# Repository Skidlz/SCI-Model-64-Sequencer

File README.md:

# SCI-Model-64-Sequencer
Sequential Circuits Model 64 Sequencer for Commodore 64

## Parts
At the time or writing, most of the parts are still available at Jameco.

They offer the H11L1 can be used in place of the PC900, and 68B21 instead of the 68A21.

## Schematic

## PCB

## Case

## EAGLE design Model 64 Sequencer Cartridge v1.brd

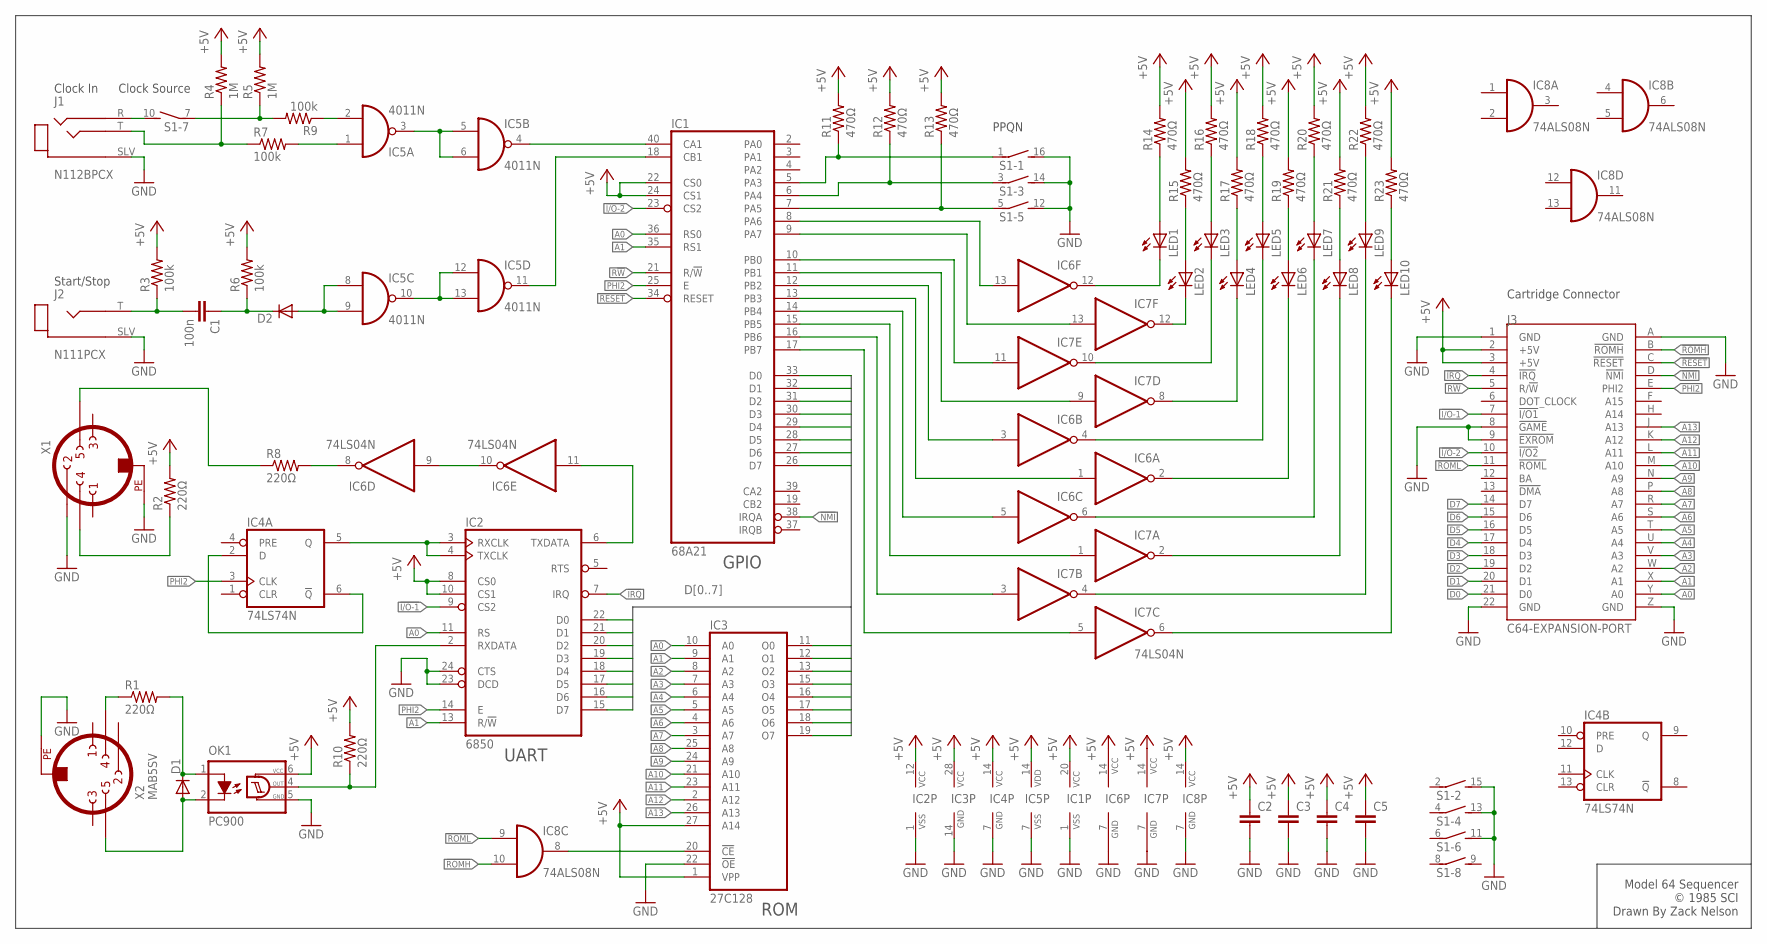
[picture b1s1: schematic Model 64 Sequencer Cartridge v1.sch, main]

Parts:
C1: 100n; C050-024X044
C2, C3, C4, C5: C-EU050-024X044; C050-024X044
D1, D2: DIODE-D-7.5; D-7.5
IC1: 68A21; DIL40
IC2: 6850; DIL24
IC3: 27C128; DIL28
IC4: 74LS74N; DIL14
IC5: 4011N; DIL14
IC6, IC7: 74LS04N; DIL14
IC8: 74ALS08N; DIL14
J1: N112BPCX; SWITCHCRAFT_N112BPCX
J2: N111PCX; SWITCHCRAFT_N111PCX
J3: C64-EXPANSION-PORT; EXPANSIO_SQ
LED1, LED2, LED3, LED4, LED5, LED6, LED7, LED8, LED9, LED10: LED3MM
OK1: PC900; DIL06
R1, R2, R8, R10: 220Ω; 0207/12
R3, R6, R7, R9: 100k; 0207/12
R4, R5: 1M; 0207/12
R11, R12, R13, R14, R15, R16, R17, R18, R19, R20, R21, R22, R23: 470Ω; 0207/12
S1: DIP08S
X1, X2: MAB5SV

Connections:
!I/O-1: IC2.9 (CS2), J3.7 (!I/O1)
!I/O-2: IC1.23 (CS2), J3.10 (!I/O2)
!IRQ: IC2.7 (IRQ), J3.4 (!IRQ)
!NMI: IC1.38 (IRQA), J3.D (!NMI)
!RESET: IC1.34 (RESET), J3.C (!RESET)
!ROMH: IC8.10 (I1), J3.B (!ROMH)
!ROML: IC8.9 (I0), J3.11 (!ROML)
+5V: C2.1, C3.1, C4.1, C5.1, IC1.20 (VCC), IC1.22 (CS0), IC1.24 (CS1), IC2.8 (CS0), IC2.10 (CS1), IC2.12 (VCC), IC3.1 (VPP), IC3.27 (A14), IC3.28 (VCC), IC4.14 (VCC), IC5.14 (VDD), IC6.14 (VCC), IC7.14 (VCC), IC8.14 (VCC), J3.2 (+5V), J3.3 (+5V), OK1.6 (VCC), R2.2, R3.2, R4.2, R5.2, R6.2, R10.2, R11.2, R12.2, R13.2, R14.2, R15.2, R16.2, R17.2, R18.2, R19.2, R20.2, R21.2, R22.2, R23.2
A0: IC1.36 (RS0), IC2.11 (RS), IC3.10 (A0), J3.Y (A0)
A1: IC1.35 (RS1), IC2.13 (R/!W), IC3.9 (A1), J3.X (A1)
A2: IC3.8 (A2), J3.W (A2)
A3: IC3.7 (A3), J3.V (A3)
A4: IC3.6 (A4), J3.U (A4)
A5: IC3.5 (A5), J3.T (A5)
A6: IC3.4 (A6), J3.S (A6)
A7: IC3.3 (A7), J3.R (A7)
A8: IC3.25 (A8), J3.P (A8)
A9: IC3.24 (A9), J3.N (A9)
A10: IC3.21 (A10), J3.M (A10)
A11: IC3.23 (A11), J3.L (A11)
A12: IC3.2 (A12), J3.K (A12)
A13: IC3.26 (A13), J3.J (A13)
D0: IC1.33 (D0), IC2.22 (D0), IC3.11 (O0), J3.21 (D0)
D1: IC1.32 (D1), IC2.21 (D1), IC3.12 (O1), J3.20 (D1)
D2: IC1.31 (D2), IC2.20 (D2), IC3.13 (O2), J3.19 (D2)
D3: IC1.30 (D3), IC2.19 (D3), IC3.15 (O3), J3.18 (D3)
D4: IC1.29 (D4), IC2.18 (D4), IC3.16 (O4), J3.17 (D4)
D5: IC1.28 (D5), IC2.17 (D5), IC3.17 (O5), J3.16 (D5)
D6: IC1.27 (D6), IC2.16 (D6), IC3.18 (O6), J3.15 (D6)
D7: IC1.26 (D7), IC2.15 (D7), IC3.19 (O7), J3.14 (D7)
GND: C2.2, C3.2, C4.2, C5.2, IC1.1 (VSS), IC2.1 (VSS), IC2.23 (DCD), IC2.24 (CTS), IC3.14 (GND), IC3.22 (!OE), IC4.7 (GND), IC5.7 (VSS), IC6.7 (GND), IC7.7 (GND), IC8.7 (GND), J1.SLV (SLEEVE), J2.SLV (SLEEVE), J3.1 (GND), J3.8 (!GAME), J3.9 (!EXROM), J3.22 (GND), J3.A (GND), J3.Z (GND), OK1.5 (GND), S1.11 (2), S1.12 (2), S1.13 (2), S1.14 (2), S1.15 (2), S1.16 (2), X1.2, X1.PE, X2.PE
unnamed: IC2.3 (RXCLK), IC2.4 (TXCLK), IC4.5 (Q)
unnamed: R2.1, X1.4
unnamed: IC2.6 (TXDATA), IC6.11 (I)
unnamed: IC4.2 (D), IC4.6 (!Q)
unnamed: IC6.9 (I), IC6.10 (O)
unnamed: IC6.8 (O), R8.2
unnamed: IC1.13 (PB3), IC6.1 (I)
unnamed: IC5.3 (O), IC5.5 (I0), IC5.6 (I1)
unnamed: D2.A, IC5.8 (I0), IC5.9 (I1)
unnamed: IC5.10 (O), IC5.12 (I0), IC5.13 (I1)
unnamed: IC1.18 (CB1), IC5.11 (O)
unnamed: IC1.40 (CA1), IC5.4 (O)
unnamed: IC5.1 (I0), R7.2
unnamed: LED6.A, R19.1
unnamed: LED5.A, R18.1
unnamed: LED7.A, R20.1
unnamed: LED1.A, R14.1
unnamed: LED2.A, R15.1
unnamed: LED8.A, R21.1
unnamed: LED9.A, R22.1
unnamed: IC7.2 (O), LED8.K (C)
unnamed: IC7.4 (O), LED9.K (C)
unnamed: IC7.6 (O), LED10.K (C)
unnamed: IC7.8 (O), LED4.K (C)
unnamed: IC7.10 (O), LED3.K (C)
unnamed: IC7.12 (O), LED2.K (C)
unnamed: LED10.A, R23.1
unnamed: LED4.A, R17.1
unnamed: LED3.A, R16.1
unnamed: IC1.5 (PA3), R11.1, S1.1
unnamed: IC1.6 (PA4), R12.1, S1.3 (1)
unnamed: IC1.7 (PA5), R13.1, S1.5 (1)
unnamed: J1.T (TIP), R4.1, R7.1
unnamed: C1.1, D2.C, R6.1
unnamed: C1.2, J2.T (TIP), R3.1
unnamed: IC5.2 (I1), R9.1
unnamed: R5.1, R9.2, S1.7 (1)
unnamed: J1.R (RING), S1.10 (2)
unnamed: D1.A, OK1.2 (C), X2.5
unnamed: D1.C, OK1.1 (A), R1.2
unnamed: IC2.2 (RXDATA), OK1.4 (OUT), R10.1
unnamed: IC6.12 (O), LED1.K (C)
unnamed: IC1.15 (PB5), IC7.1 (I)
unnamed: IC1.9 (PA7), IC7.13 (I)
unnamed: IC1.16 (PB6), IC7.3 (I)
unnamed: IC1.17 (PB7), IC7.5 (I)
unnamed: IC1.11 (PB1), IC7.9 (I)
unnamed: IC1.10 (PB0), IC7.11 (I)
unnamed: IC1.8 (PA6), IC6.13 (I)
unnamed: IC6.6 (O), LED7.K (C)
unnamed: IC1.14 (PB4), IC6.5 (I)
unnamed: IC1.12 (PB2), IC6.3 (I)
unnamed: IC6.4 (O), LED5.K (C)
unnamed: IC6.2 (O), LED6.K (C)
unnamed: R8.1, X1.5
unnamed: R1.1, X2.4
unnamed: IC3.20 (!CE), IC8.8 (O)
PHI2: IC1.25 (E), IC2.14 (E), IC4.3 (CLK), J3.E (PHI2)
R!W: IC1.21 (R/!W), J3.5 (R/!W)

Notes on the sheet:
Model 64 Sequencer © 1985 SCI Drawn By Zack Nelson
UART
ROM
GPIO
PPQN
Clock Source
Start/Stop
Clock In
Cartridge Connector

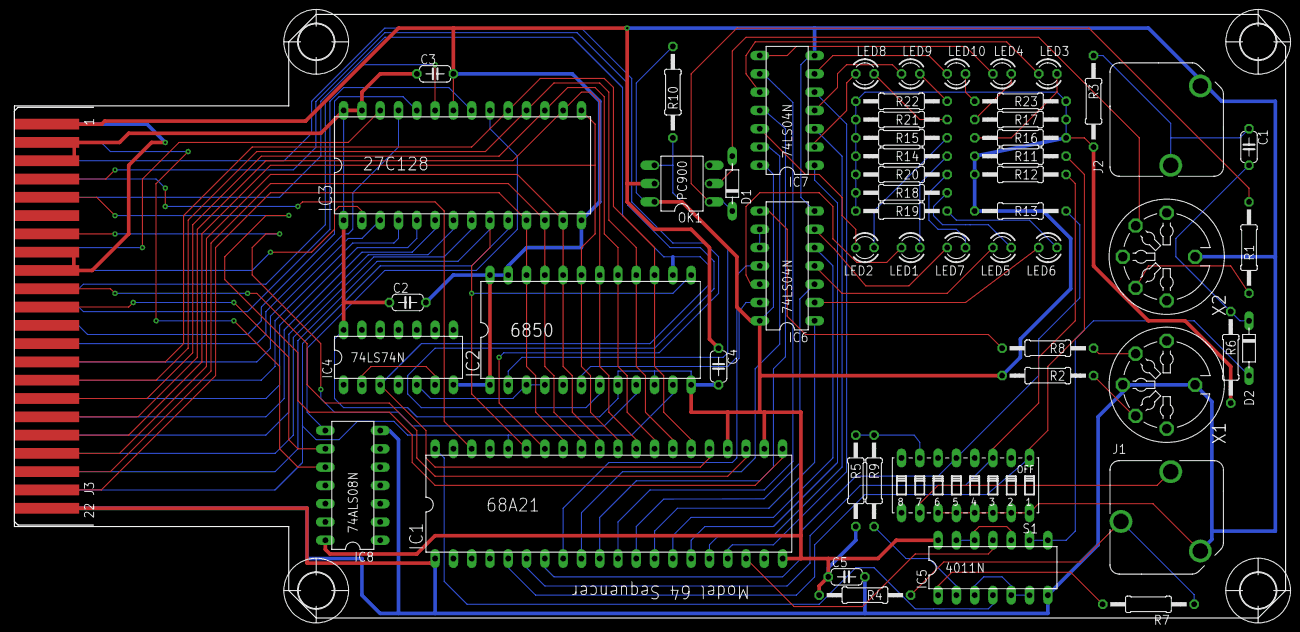
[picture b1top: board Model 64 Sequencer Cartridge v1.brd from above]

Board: 2 copper layers, 176.5 x 83.8 mm, 59 parts (0 on the bottom side), 90 nets.

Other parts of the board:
U$1, U$2, U$3, U$4: 5,0

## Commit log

2025-03-26 Update to use 6.35mm jacks
2025-03-27 Fixing names on wrong layer
2025-04-02 Adding EPROM dump
2025-04-03 Adding service manual scan
